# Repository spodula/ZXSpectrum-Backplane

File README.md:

# ZXSpectrum-Backplane
4 way ZX spectrum backplane with option for external power. 

Version 2: 16 July 2022
On V1, the sockets were reversed to what was required. This is corrected on V2.

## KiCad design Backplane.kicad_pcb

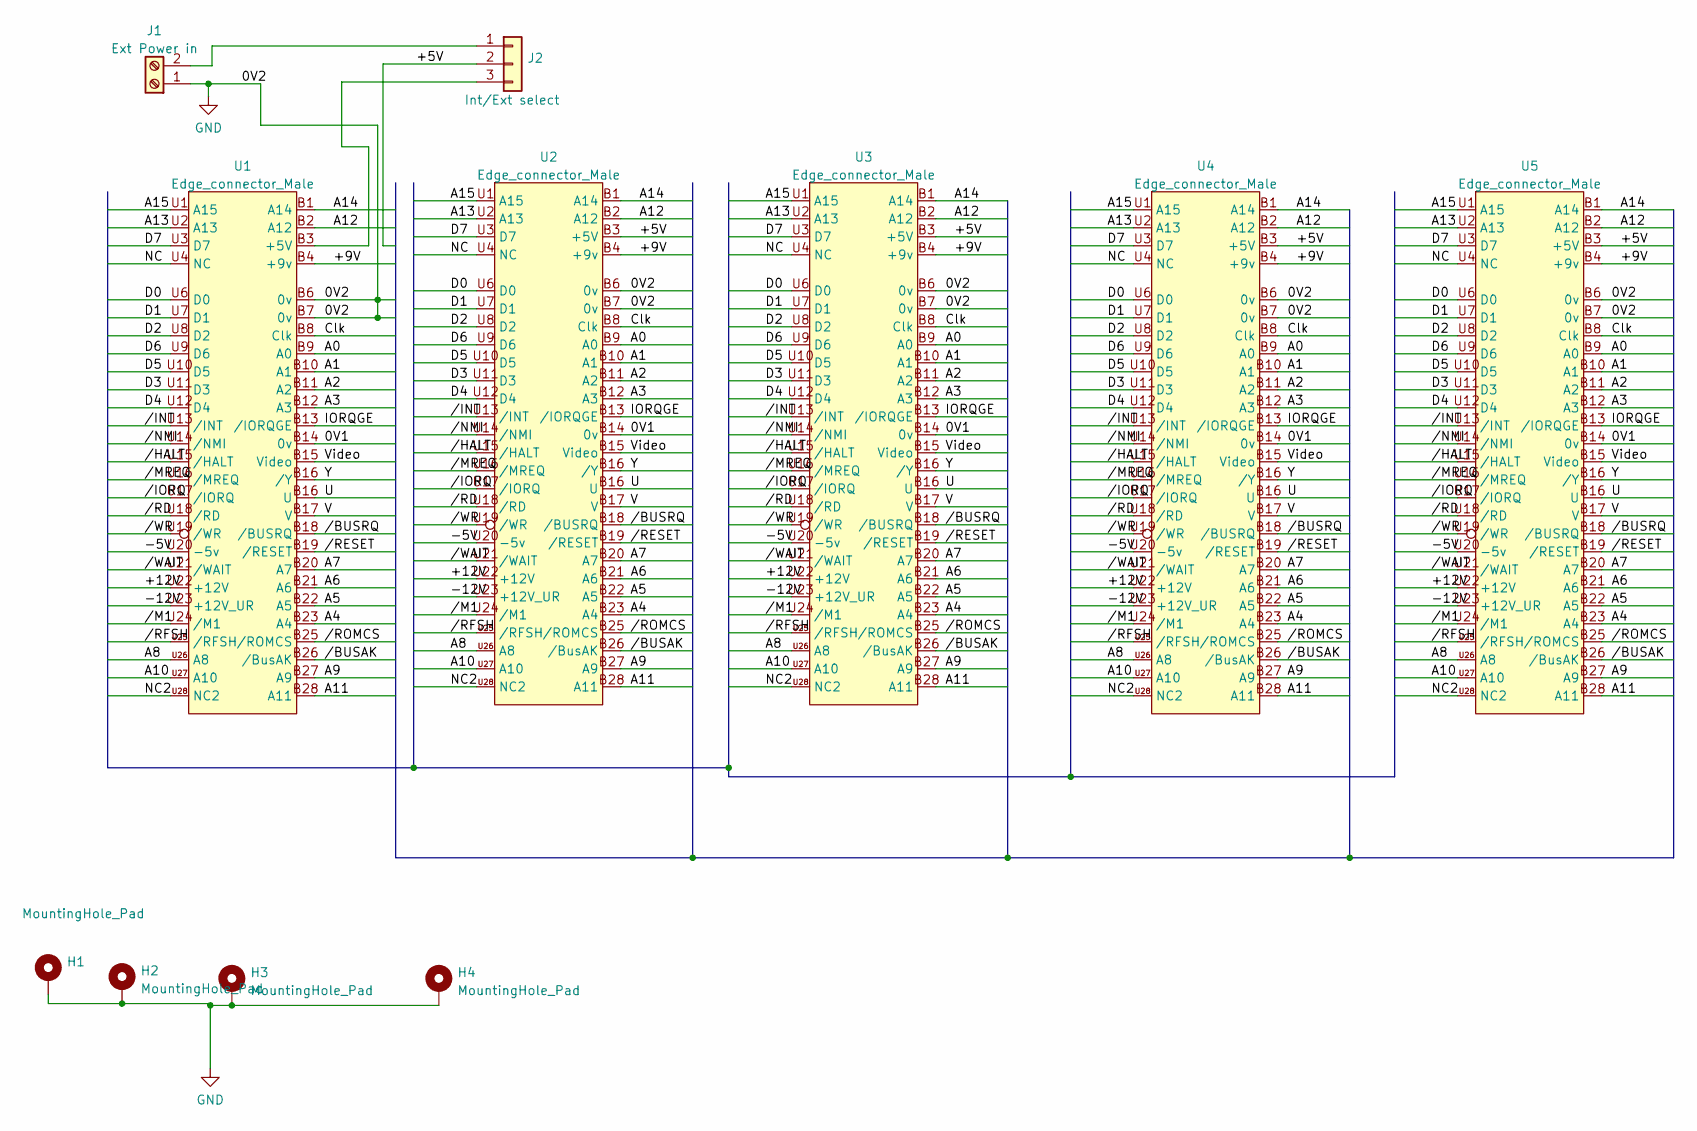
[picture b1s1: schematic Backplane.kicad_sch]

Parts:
H1, H2, H3, H4: MountingHole_Pad; MountingHole_2.5mm_Pad
J1: Ext Power in; TerminalBlock_bornier-2_P5.08mm
J2: Int/Ext select; PinSocket_1x03_P2.54mm_Vertical
U1: Edge_connector_Male; Speccy_edge_External
U2, U3, U4, U5: Edge_connector_Male; Speccy_edge_Socket_reversed

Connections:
/0V1: U1.B14 (0v), U2.B14 (0v), U3.B14 (0v), U4.B14 (0v), U5.B14 (0v)
/+5V: J2.2, U2.B3 (+5V), U3.B3 (+5V), U4.B3 (+5V), U5.B3 (+5V)
/+9V: U1.B4 (+9v), U2.B4 (+9v), U3.B4 (+9v), U4.B4 (+9v), U5.B4 (+9v)
/+12V: U1.U22 (+12V), U2.U22 (+12V), U3.U22 (+12V), U4.U22 (+12V), U5.U22 (+12V)
/-5V: U1.U20 (-5v), U2.U20 (-5v), U3.U20 (-5v), U4.U20 (-5v), U5.U20 (-5v)
/-12V: U1.U23 (+12V_UR), U2.U23 (+12V_UR), U3.U23 (+12V_UR), U4.U23 (+12V_UR), U5.U23 (+12V_UR)
/A0: U1.B9 (A0), U2.B9 (A0), U3.B9 (A0), U4.B9 (A0), U5.B9 (A0)
/A1: U1.B10 (A1), U2.B10 (A1), U3.B10 (A1), U4.B10 (A1), U5.B10 (A1)
/A2: U1.B11 (A2), U2.B11 (A2), U3.B11 (A2), U4.B11 (A2), U5.B11 (A2)
/A3: U1.B12 (A3), U2.B12 (A3), U3.B12 (A3), U4.B12 (A3), U5.B12 (A3)
/A4: U1.B23 (A4), U2.B23 (A4), U3.B23 (A4), U4.B23 (A4), U5.B23 (A4)
/A5: U1.B22 (A5), U2.B22 (A5), U3.B22 (A5), U4.B22 (A5), U5.B22 (A5)
/A6: U1.B21 (A6), U2.B21 (A6), U3.B21 (A6), U4.B21 (A6), U5.B21 (A6)
/A7: U1.B20 (A7), U2.B20 (A7), U3.B20 (A7), U4.B20 (A7), U5.B20 (A7)
/A8: U1.U26 (A8), U2.U26 (A8), U3.U26 (A8), U4.U26 (A8), U5.U26 (A8)
/A9: U1.B27 (A9), U2.B27 (A9), U3.B27 (A9), U4.B27 (A9), U5.B27 (A9)
/A10: U1.U27 (A10), U2.U27 (A10), U3.U27 (A10), U4.U27 (A10), U5.U27 (A10)
/A11: U1.B28 (A11), U2.B28 (A11), U3.B28 (A11), U4.B28 (A11), U5.B28 (A11)
/A12: U1.B2 (A12), U2.B2 (A12), U3.B2 (A12), U4.B2 (A12), U5.B2 (A12)
/A13: U1.U2 (A13), U2.U2 (A13), U3.U2 (A13), U4.U2 (A13), U5.U2 (A13)
/A14: U1.B1 (A14), U2.B1 (A14), U3.B1 (A14), U4.B1 (A14), U5.B1 (A14)
/A15: U1.U1 (A15), U2.U1 (A15), U3.U1 (A15), U4.U1 (A15), U5.U1 (A15)
/Clk: U1.B8 (Clk), U2.B8 (Clk), U3.B8 (Clk), U4.B8 (Clk), U5.B8 (Clk)
/D0: U1.U6 (D0), U2.U6 (D0), U3.U6 (D0), U4.U6 (D0), U5.U6 (D0)
/D1: U1.U7 (D1), U2.U7 (D1), U3.U7 (D1), U4.U7 (D1), U5.U7 (D1)
/D2: U1.U8 (D2), U2.U8 (D2), U3.U8 (D2), U4.U8 (D2), U5.U8 (D2)
/D3: U1.U11 (D3), U2.U11 (D3), U3.U11 (D3), U4.U11 (D3), U5.U11 (D3)
/D4: U1.U12 (D4), U2.U12 (D4), U3.U12 (D4), U4.U12 (D4), U5.U12 (D4)
/D5: U1.U10 (D5), U2.U10 (D5), U3.U10 (D5), U4.U10 (D5), U5.U10 (D5)
/D6: U1.U9 (D6), U2.U9 (D6), U3.U9 (D6), U4.U9 (D6), U5.U9 (D6)
/D7: U1.U3 (D7), U2.U3 (D7), U3.U3 (D7), U4.U3 (D7), U5.U3 (D7)
/IORQGE: U1.B13 (/IORQGE), U2.B13 (/IORQGE), U3.B13 (/IORQGE), U4.B13 (/IORQGE), U5.B13 (/IORQGE)
/NC: U1.U4 (NC), U2.U4 (NC), U3.U4 (NC), U4.U4 (NC), U5.U4 (NC)
/NC2: U1.U28 (NC2), U2.U28 (NC2), U3.U28 (NC2), U4.U28 (NC2), U5.U28 (NC2)
/V: U1.B17 (V), U2.B17 (V), U3.B17 (V), U4.B17 (V), U5.B17 (V)
/Video: U1.B15 (Video), U2.B15 (Video), U3.B15 (Video), U4.B15 (Video), U5.B15 (Video)
//BUSAK: U1.B26 (/BusAK), U2.B26 (/BusAK), U3.B26 (/BusAK), U4.B26 (/BusAK), U5.B26 (/BusAK)
//BUSRQ: U1.B18 (/BUSRQ), U2.B18 (/BUSRQ), U3.B18 (/BUSRQ), U4.B18 (/BUSRQ), U5.B18 (/BUSRQ)
//HALT: U1.U15 (/HALT), U2.U15 (/HALT), U3.U15 (/HALT), U4.U15 (/HALT), U5.U15 (/HALT)
//INT: U1.U13 (/INT), U2.U13 (/INT), U3.U13 (/INT), U4.U13 (/INT), U5.U13 (/INT)
//IORQ: U1.U17 (/IORQ), U2.U17 (/IORQ), U3.U17 (/IORQ), U4.U17 (/IORQ), U5.U17 (/IORQ)
//M1: U1.U24 (/M1), U2.U24 (/M1), U3.U24 (/M1), U4.U24 (/M1), U5.U24 (/M1)
//MREQ: U1.U16 (/MREQ), U2.U16 (/MREQ), U3.U16 (/MREQ), U4.U16 (/MREQ), U5.U16 (/MREQ)
//NMI: U1.U14 (/NMI), U2.U14 (/NMI), U3.U14 (/NMI), U4.U14 (/NMI), U5.U14 (/NMI)
//RD: U1.U18 (/RD), U2.U18 (/RD), U3.U18 (/RD), U4.U18 (/RD), U5.U18 (/RD)
//RESET: U1.B19 (/RESET), U2.B19 (/RESET), U3.B19 (/RESET), U4.B19 (/RESET), U5.B19 (/RESET)
//RFSH: U1.U25 (/RFSH), U2.U25 (/RFSH), U3.U25 (/RFSH), U4.U25 (/RFSH), U5.U25 (/RFSH)
//ROMCS: U1.B25 (/ROMCS), U2.B25 (/ROMCS), U3.B25 (/ROMCS), U4.B25 (/ROMCS), U5.B25 (/ROMCS)
//WAIT: U1.U21 (/WAIT), U2.U21 (/WAIT), U3.U21 (/WAIT), U4.U21 (/WAIT), U5.U21 (/WAIT)
//WR: U1.U19 (/WR), U2.U19 (/WR), U3.U19 (/WR), U4.U19 (/WR), U5.U19 (/WR)
GND: H1.1, H2.1, H3.1, H4.1, J1.1, U1.B6 (0v), U1.B7 (0v), U2.B6 (0v), U2.B7 (0v), U3.B6 (0v), U3.B7 (0v), U4.B6 (0v), U4.B7 (0v), U5.B6 (0v), U5.B7 (0v)
unnamed: J1.2, J2.1
unnamed: J2.3, U1.B3 (+5V)

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
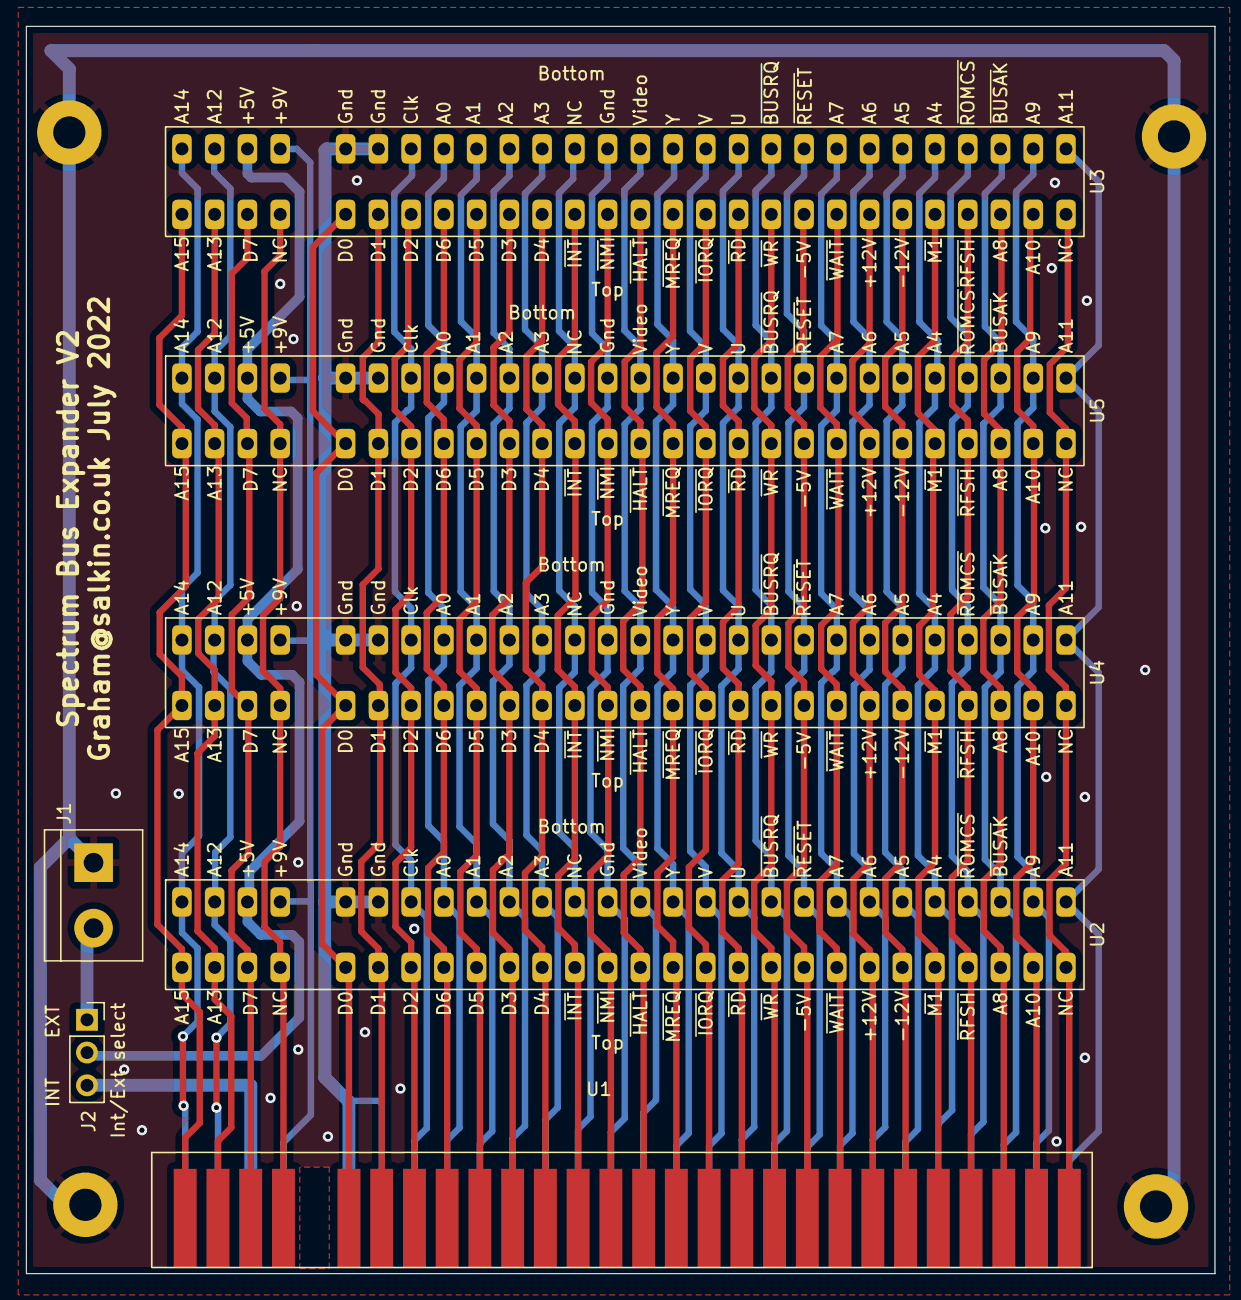
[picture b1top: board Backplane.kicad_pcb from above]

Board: 2 copper layers, 92.2 x 96.7 mm, 11 parts (0 on the bottom side), 54 nets.

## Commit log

2022-06-21 Corrected edge connector bound box
2022-07-16 Updated footprints. Also added reversed socket
2022-07-16 Added updated PCB and images. Corrected the fact the sockets were reversed
